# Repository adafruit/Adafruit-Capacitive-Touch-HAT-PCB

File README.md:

## Adafruit Capacitive Touch HAT PCB
<a href="http://www.adafruit.com/products/2340"><br/>
Click here to purchase one from the Adafruit shop</a>

This touch-able add on HAT for Raspberry Pi will inspire your next interactive project with 12 capacitive touch sensors. Capacitive touch sensing works by detecting when a person (or animal) has touched one of the sensor electrodes. Capacitive touch sensing used for stuff like touch-reactive tablets and phones, as well as control panels for appliances, which is where you may have used it before. This HAT allows you to create electronics that can react to human touch, with up to 12 individual sensors.

The HAT has 12 'figure 8' holes in it that can be gripped onto with alligator clip cables. Attach one side of the clip to the HAT and the other side to something electrically conductive (like metal) or full of water (like vegetables or fruit!) Then start up our handy Python library code to detect when the object is touched. That's pretty much it, very easy! For advanced users, you can also solder to a pad to make a slimmer & more permanent connection.

PCB files for the Adafruit Capacitive Touch HAT. The format is EagleCAD schematic and board layout
- https://www.adafruit.com/products/2340

### License

Adafruit invests time and resources providing this open source design, please support Adafruit and open-source hardware by purchasing products from [Adafruit](https://www.adafruit.com)!

All text above must be included in any redistribution

Designed by Limor Fried/Ladyada for Adafruit Industries.
Creative Commons Attribution/Share-Alike, all text above must be included in any redistribution. 
See license.txt for additional information.

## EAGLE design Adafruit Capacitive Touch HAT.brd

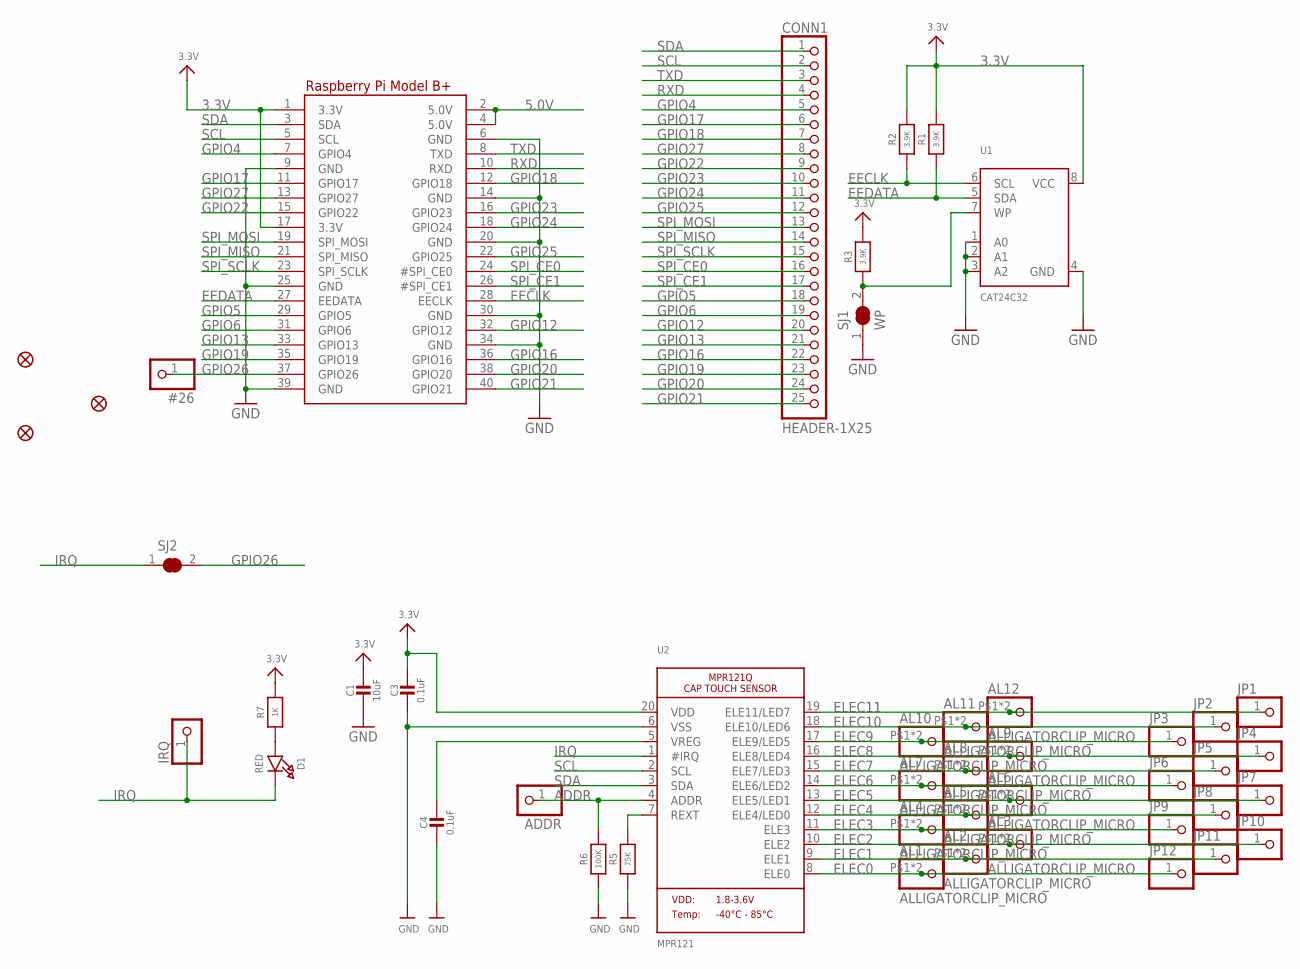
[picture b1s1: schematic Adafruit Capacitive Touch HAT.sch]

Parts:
#26: HEADER-1X1ROUND; 1X01_ROUND
ADDR: HEADER-1X1ROUND; 1X01_ROUND
AL1, AL2, AL3, AL4, AL5, AL6, AL7, AL8, AL9, AL10, AL11, AL12: ALLIGATORCLIP_MICRO; ALLIGATORCLIP
C1: 10uF; 0805-NO
C3, C4: 0.1uF; 0805-NO
CONN1: HEADER-1X25; 1X25_ROUND_70MIL
D1: RED; CHIPLED_0805_NOOUTLINE
FID1, FID2, FID3: FIDUCIAL""; FIDUCIAL_1MM
IRQ: HEADER-1X1ROUND; 1X01_ROUND
JP1, JP2, JP3, JP4, JP5, JP6, JP7, JP8, JP9, JP10, JP11, JP12: HEADER-1X1ROUND; 1X01_ROUND
R1, R2, R3: 3.9K; 0805-NO
R5: 75K; 0805-NO
R6: 100K; 0805-NO
R7: 1K; 0805-NO
RPI1: RASPBERRYPI_BPLUS_HATSLOTS; PI_HAT_SLOTS
SJ1: WP; SOLDERJUMPER_CLOSEDWIRE
SJ2: SOLDERJUMPER_CLOSED; SOLDERJUMPER_CLOSEDWIRE
U1: CAT24C32; SOIC8_150MIL
U2: MPR121; QFN20_3MM_NOTHERMAL

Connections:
3.3V: C1.1, C3.1, R1.2, R2.2, R3.2, R7.2, RPI1.1 (3.3V), RPI1.17 (3.3V), U1.8 (VCC), U2.20 (VDD)
5.0V: RPI1.2 (5.0V), RPI1.4 (5.0V)
ADDR: ADDR.1, R6.2, U2.4 (ADDR)
EECLK: R2.1, RPI1.28 (EECLK), U1.6 (SCL)
EEDATA: R1.1, RPI1.27 (EEDATA), U1.5 (SDA)
ELEC0: AL1.P$1, AL1.P$2, JP12.1, U2.8 (ELE0)
ELEC1: AL2.P$1, AL2.P$2, JP11.1, U2.9 (ELE1)
ELEC2: AL3.P$1, AL3.P$2, JP10.1, U2.10 (ELE2)
ELEC3: AL4.P$1, AL4.P$2, JP9.1, U2.11 (ELE3)
ELEC4: AL5.P$1, AL5.P$2, JP8.1, U2.12 (ELE4/LED0)
ELEC5: AL6.P$1, AL6.P$2, JP7.1, U2.13 (ELE5/LED1)
ELEC6: AL7.P$1, AL7.P$2, JP6.1, U2.14 (ELE6/LED2)
ELEC7: AL8.P$1, AL8.P$2, JP5.1, U2.15 (ELE7/LED3)
ELEC8: AL9.P$1, AL9.P$2, JP4.1, U2.16 (ELE8/LED4)
ELEC9: AL10.P$1, AL10.P$2, JP3.1, U2.17 (ELE9/LED5)
ELEC10: AL11.P$1, AL11.P$2, JP2.1, U2.18 (ELE10/LED6)
ELEC11: AL12.P$1, AL12.P$2, JP1.1, U2.19 (ELE11/LED7)
GND: C1.2, C3.2, C4.2, R5.1, R6.1, RPI1.6 (GND), RPI1.9 (GND), RPI1.14 (GND), RPI1.20 (GND), RPI1.25 (GND), RPI1.30 (GND), RPI1.34 (GND), RPI1.39 (GND), SJ1.1, U1.1 (A0), U1.2 (A1), U1.3 (A2), U1.4 (GND), U2.6 (VSS)
GPIO4: CONN1.5, RPI1.7 (GPIO4)
GPIO5: CONN1.18, RPI1.29 (GPIO5)
GPIO6: CONN1.19, RPI1.31 (GPIO6)
GPIO12: CONN1.20, RPI1.32 (GPIO12)
GPIO13: CONN1.21, RPI1.33 (GPIO13)
GPIO16: CONN1.22, RPI1.36 (GPIO16)
GPIO17: CONN1.6, RPI1.11 (GPIO17)
GPIO18: CONN1.7, RPI1.12 (GPIO18)
GPIO19: CONN1.23, RPI1.35 (GPIO19)
GPIO20: CONN1.24, RPI1.38 (GPIO20)
GPIO21: CONN1.25, RPI1.40 (GPIO21)
GPIO22: CONN1.9, RPI1.15 (GPIO22)
GPIO23: CONN1.10, RPI1.16 (GPIO23)
GPIO24: CONN1.11, RPI1.18 (GPIO24)
GPIO25: CONN1.12, RPI1.22 (GPIO25)
GPIO26: #26.1, RPI1.37 (GPIO26), SJ2.2
GPIO27: CONN1.8, RPI1.13 (GPIO27)
IRQ: D1.C, IRQ.1, SJ2.1, U2.1 (#IRQ)
unnamed: R3.1, SJ1.2, U1.7 (WP)
unnamed: C4.1, U2.5 (VREG)
unnamed: R5.2, U2.7 (REXT)
unnamed: D1.A, R7.1
RXD: CONN1.4, RPI1.10 (RXD)
SCL: CONN1.2, RPI1.5 (SCL), U2.2 (SCL)
SDA: CONN1.1, RPI1.3 (SDA), U2.3 (SDA)
SPI_CE0: CONN1.16, RPI1.24 (#SPI_CE0)
SPI_CE1: CONN1.17, RPI1.26 (#SPI_CE1)
SPI_MISO: CONN1.14, RPI1.21 (SPI_MISO)
SPI_MOSI: CONN1.13, RPI1.19 (SPI_MOSI)
SPI_SCLK: CONN1.15, RPI1.23 (SPI_SCLK)
TXD: CONN1.3, RPI1.8 (TXD)

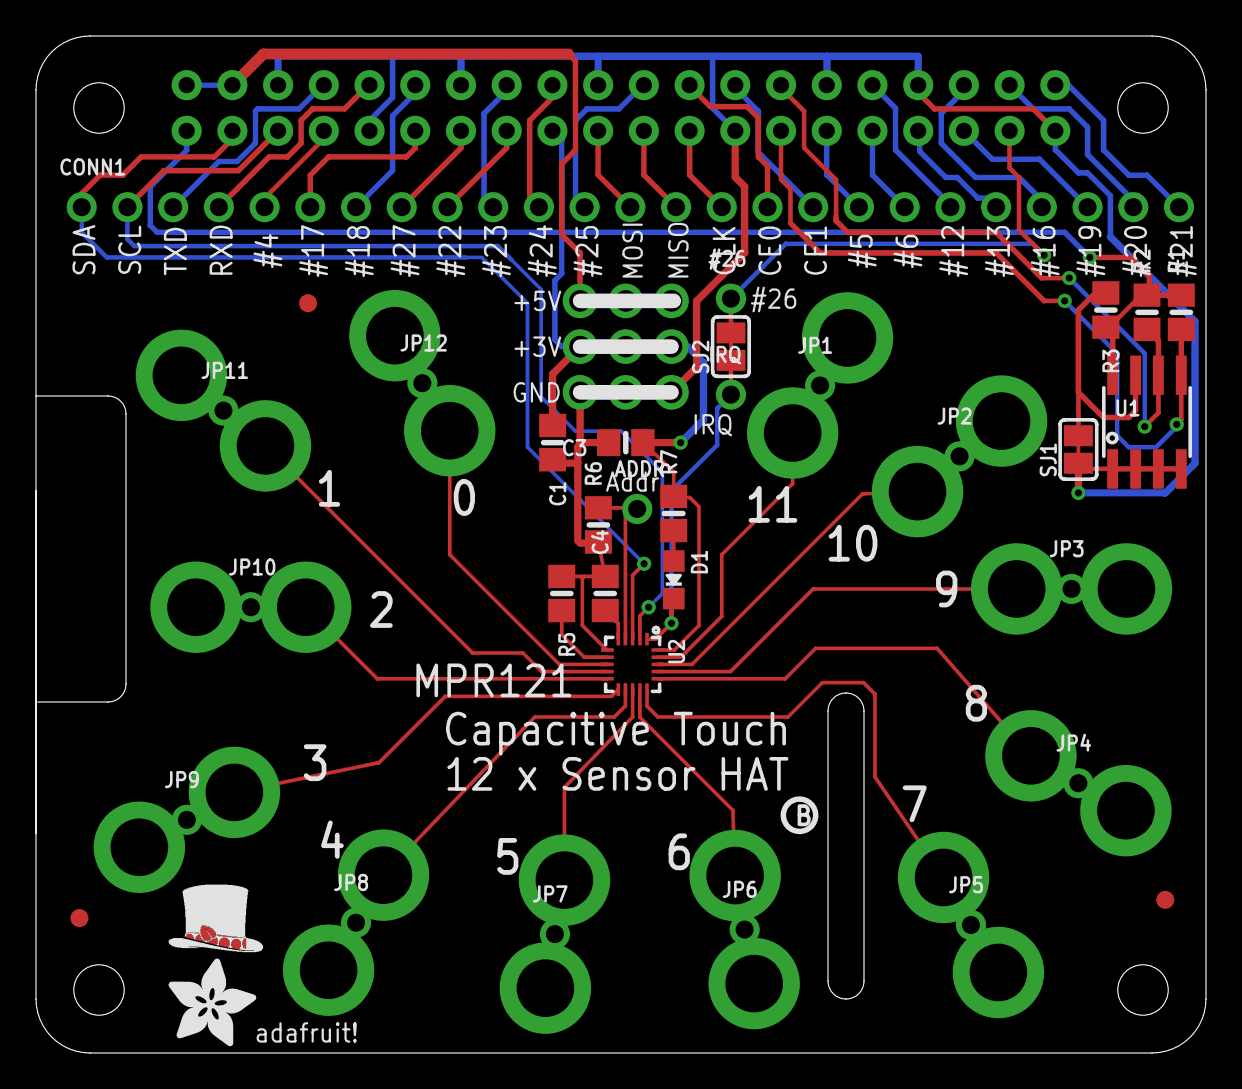
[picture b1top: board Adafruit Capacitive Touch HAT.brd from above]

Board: 2 copper layers, 65.0 x 56.5 mm, 49 parts (0 on the bottom side), 49 nets.

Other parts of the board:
U$5: PIHATLOGO
U$6: PCBFEAT-REV-040
U$51: ADAFRUIT_5MM

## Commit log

2016-07-12 capinit

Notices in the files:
parts and their libraries:
microbuilder: This work is placed in the public domain, and may be freely used for commercial and non-commercial work with the following conditions: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
